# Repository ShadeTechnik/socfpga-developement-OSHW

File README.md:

# socfpga-developement-OSHW
hardware and software development for socfpga, open source

Copyright 2019 Shade Technik

<br />This work is licensed under a <a rel="license" href="http://creativecommons.org/licenses/by-sa/4.0/">Creative Commons Attribution-ShareAlike 4.0 International License</a>.

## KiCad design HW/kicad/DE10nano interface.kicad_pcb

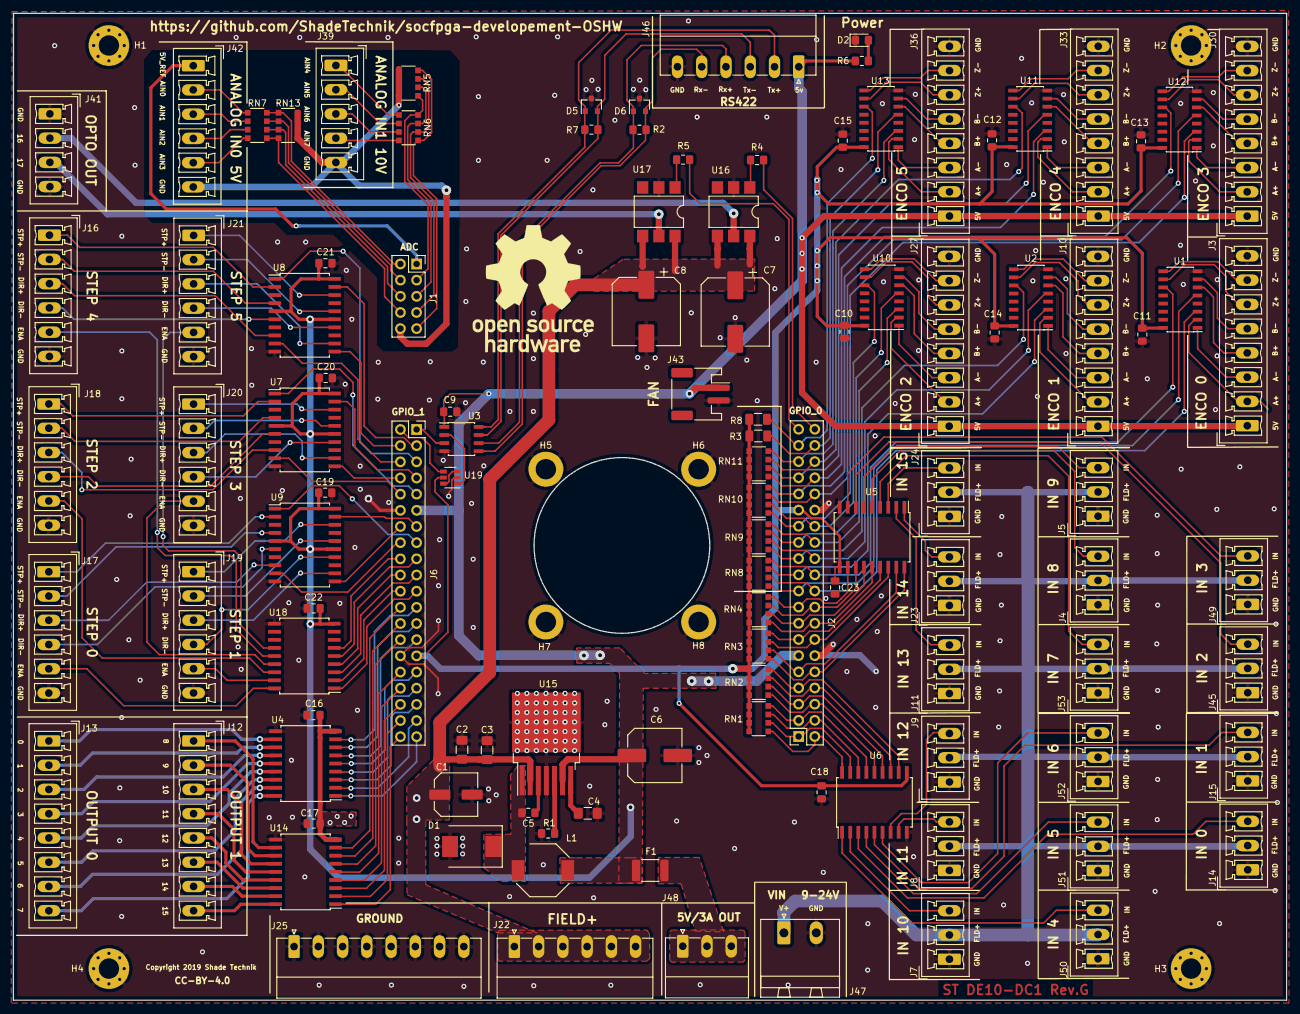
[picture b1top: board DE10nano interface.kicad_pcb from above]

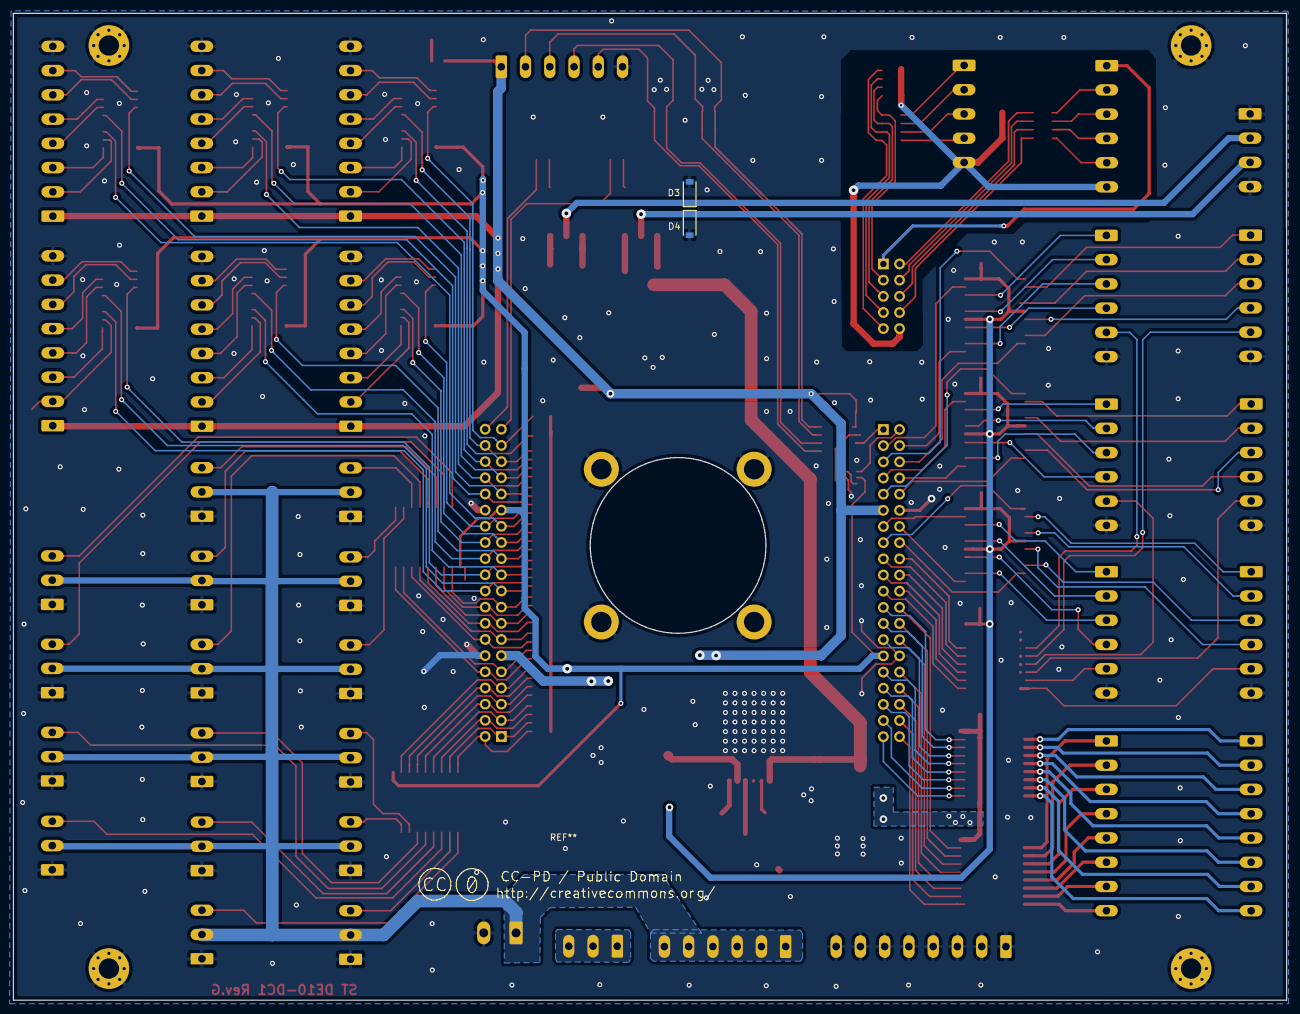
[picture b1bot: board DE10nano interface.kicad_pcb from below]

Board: 2 copper layers, 200.0 x 155.0 mm, 120 parts (2 on the bottom side), 208 nets.

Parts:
C1: 22uf; C_Elec_6.3x7.7
C2, C3: 6.8uf; C_1206_3216Metric_Pad1.42x1.75mm_HandSolder
C4: 1uf; C_1206_3216Metric_Pad1.42x1.75mm_HandSolder
C5: 10nF; C_0805_2012Metric_Pad1.15x1.40mm_HandSolder
C6: 180uF; C_Elec_8x10.2
C7, C8: 100uF; CP_Elec_10x10.5
C9: 0.1uF; C_0805_2012Metric_Pad1.15x1.40mm_HandSolder
C10, C11, C12, C13, C14, C15, C16, C17, C18, C19, C20, C21, C22, C23: .1uf; C_0805_2012Metric_Pad1.15x1.40mm_HandSolder
D1: 60v 5a; D_SMC
D2: LED_PWR; LED_0805_2012Metric_Pad1.15x1.40mm_HandSolder
D3, D4: D_Schottky; D_SOD-123
D5, D6: SM712; SOT-23
F1: 1.5Ahold/3Atrip; Fuse_1812_4532Metric_Pad1.30x3.40mm_HandSolder
H1, H2, H3, H4: MountingHole_Pad; MountingHole_3.2mm_M3_Pad_Via
H5, H6, H7, H8: MountingHole_Pad; MountingHole_3.2mm_M3_ISO14580_Pad
J1: DE0_ADC; PinSocket_2x05_P2.54mm_Vertical
J2: DE0_GPIO_0; PinSocket_2x20_P2.54mm_Vertical
J3: ENC0_IN; PhoenixContact_MCV_1,5_8-G-3.81_1x08_P3.81mm_Vertical
J4: Conn_In_8; PhoenixContact_MCV_1,5_3-G-3.81_1x03_P3.81mm_Vertical
J5: Conn_In_9; PhoenixContact_MCV_1,5_3-G-3.81_1x03_P3.81mm_Vertical
J6: DE0_GPIO_1; PinSocket_2x20_P2.54mm_Vertical
J7: Conn_In_10; PhoenixContact_MCV_1,5_3-G-3.81_1x03_P3.81mm_Vertical
J8: Conn_In_11; PhoenixContact_MCV_1,5_3-G-3.81_1x03_P3.81mm_Vertical
J9: Conn_In_12; PhoenixContact_MCV_1,5_3-G-3.81_1x03_P3.81mm_Vertical
J10: ENC1_IN; PhoenixContact_MCV_1,5_8-G-3.81_1x08_P3.81mm_Vertical
J11: Conn_In_13; PhoenixContact_MCV_1,5_3-G-3.81_1x03_P3.81mm_Vertical
J12: Conn_Out_1; PhoenixContact_MCV_1,5_8-G-3.81_1x08_P3.81mm_Vertical
J13: Conn_Out_0; PhoenixContact_MCV_1,5_8-G-3.81_1x08_P3.81mm_Vertical
J14: Conn_In_0; PhoenixContact_MCV_1,5_3-G-3.81_1x03_P3.81mm_Vertical
J15: Conn_In_1; PhoenixContact_MCV_1,5_3-G-3.81_1x03_P3.81mm_Vertical
J16: StepGen4; PhoenixContact_MCV_1,5_6-G-3.81_1x06_P3.81mm_Vertical
J17: StepGen0; PhoenixContact_MCV_1,5_6-G-3.81_1x06_P3.81mm_Vertical
J18: StepGen2; PhoenixContact_MCV_1,5_6-G-3.81_1x06_P3.81mm_Vertical
J19: StepGen1; PhoenixContact_MCV_1,5_6-G-3.81_1x06_P3.81mm_Vertical
J20: StepGen3; PhoenixContact_MCV_1,5_6-G-3.81_1x06_P3.81mm_Vertical
J21: StepGen5; PhoenixContact_MCV_1,5_6-G-3.81_1x06_P3.81mm_Vertical
J22: Conn_Field+; PhoenixContact_MC_1,5_6-G-3.81_1x06_P3.81mm_Horizontal
J23: Conn_In_14; PhoenixContact_MCV_1,5_3-G-3.81_1x03_P3.81mm_Vertical
J24: Conn_In_15; PhoenixContact_MCV_1,5_3-G-3.81_1x03_P3.81mm_Vertical
J25: Conn_01x08-Connector_Generic; PhoenixContact_MC_1,5_8-G-3.81_1x08_P3.81mm_Horizontal
J27: ENC2_IN; PhoenixContact_MCV_1,5_8-G-3.81_1x08_P3.81mm_Vertical
J30: ENC3_IN; PhoenixContact_MCV_1,5_8-G-3.81_1x08_P3.81mm_Vertical
J33: ENC4_IN; PhoenixContact_MCV_1,5_8-G-3.81_1x08_P3.81mm_Vertical
J36: ENC5_IN; PhoenixContact_MCV_1,5_8-G-3.81_1x08_P3.81mm_Vertical
J39: Conn_ADC_1_10V; PhoenixContact_MCV_1,5_5-G-3.81_1x05_P3.81mm_Vertical
J41: Conn_Opto_out; PhoenixContact_MCV_1,5_4-G-3.81_1x04_P3.81mm_Vertical
J42: Conn_ADC_0_5V; PhoenixContact_MCV_1,5_6-G-3.81_1x06_P3.81mm_Vertical
J43: Conn_Fan; JST_PH_S2B-PH-SM4-TB_1x02-1MP_P2.00mm_Horizontal
J45: Conn_In_2; PhoenixContact_MCV_1,5_3-G-3.81_1x03_P3.81mm_Vertical
J46: Conn_RS422; PhoenixContact_MC_1,5_6-G-3.81_1x06_P3.81mm_Horizontal
J47: Conn_VIN; PhoenixContact_MSTBA_2,5_2-G-5,08_1x02_P5.08mm_Horizontal
J48: Conn_5v; PhoenixContact_MC_1,5_3-G-3.81_1x03_P3.81mm_Horizontal
J49: Conn_In_3; PhoenixContact_MCV_1,5_3-G-3.81_1x03_P3.81mm_Vertical
J50: Conn_In_4; PhoenixContact_MCV_1,5_3-G-3.81_1x03_P3.81mm_Vertical
J51: Conn_In_5; PhoenixContact_MCV_1,5_3-G-3.81_1x03_P3.81mm_Vertical
J52: Conn_In_6; PhoenixContact_MCV_1,5_3-G-3.81_1x03_P3.81mm_Vertical
J53: Conn_In_7; PhoenixContact_MCV_1,5_3-G-3.81_1x03_P3.81mm_Vertical
L1: 4.7uH; L_Bourns-SRU8043
R1: 8k2; R_0805_2012Metric_Pad1.15x1.40mm_HandSolder
R2, R7: 120R; R_0805_2012Metric_Pad1.15x1.40mm_HandSolder
R3, R8: 4.7k; R_1206_3216Metric
R4, R5: 680R; R_0805_2012Metric_Pad1.15x1.40mm_HandSolder
R6: 180R; R_0805_2012Metric_Pad1.15x1.40mm_HandSolder
RN1, RN2, RN3, RN4, RN8, RN9, RN10, RN11: 4.7k; R_Array_Convex_4x1206
RN5, RN13: 10k; R_Array_Convex_4x1206
RN6: 15k; R_Array_Convex_4x1206
RN7: 2.2k; R_Array_Convex_4x1206
U1, U2, U10, U11, U12, U13: AM26LS32; SOIC-16_3.9x9.9mm_P1.27mm
U3: DS89C21; SOIC-8_3.9x4.9mm_P1.27mm
U4, U14, U18: MIC2981; SOIC-18W_7.5x11.6mm_P1.27mm
U5, U6: ULN2803A; SOIC-18W_7.5x11.6mm_P1.27mm
U7, U8, U9: SN75174DWR; SOIC-20W_7.5x12.8mm_P1.27mm
U15: LM22679; TO-263-7_TabPin4
U16, U17: SMP-1A36-6S; SMDIP-6_W7.62mm
U19: 74LVC2G04; SOT-23-6

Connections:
3.3v: C10.2, C11.2, C12.2, C13.2, C14.2, C15.2, C18.2, C23.2, J2.29, J6.29, R3.2, R8.2, RN1.1, RN1.2, RN1.3, RN1.4, RN2.1, RN2.2, RN2.3, RN2.4, RN3.1, RN3.2, RN3.3, RN3.4, RN4.1, RN4.2, RN4.3, RN4.4, RN8.1, RN8.2, RN8.3, RN8.4, RN9.1, RN9.2, RN9.3, RN9.4, RN10.1, RN10.2, RN10.3, RN10.4, RN11.1, RN11.2, RN11.3, RN11.4, U1.16, U2.16, U5.10, U6.10, U10.16, U11.16, U12.16, U13.16, U19.5
5v: C6.1, C9.2, C19.2, C20.2, C21.2, C22.2, F1.2, J2.11, J3.1, J6.11, J10.1, J27.1, J30.1, J33.1, J36.1, J43.1, J46.1, L1.2, R6.1, U3.1, U7.5, U7.15, U7.20, U8.5, U8.15, U8.20, U9.5, U9.15, U9.20, U15.6, U18.9
5v_ADC_REF: J1.1, J42.1
/Output Interface/0: J13.1, U4.11
/Output Interface/1: J13.2, U4.12
/Output Interface/2: J13.3, U4.13
/Output Interface/3: J13.4, U4.14
/Output Interface/4: J13.5, U4.15
/Output Interface/5: J13.6, U4.16
/Output Interface/6: J13.7, U4.17
/Output Interface/7: J13.8, U4.18
/Output Interface/8: J12.1, U14.11
/Output Interface/9: J12.2, U14.12
/Output Interface/10: J12.3, U14.13
/Output Interface/11: J12.4, U14.14
/Output Interface/12: J12.5, U14.15
/Output Interface/13: J12.6, U14.16
/Output Interface/14: J12.7, U14.17
/Output Interface/15: J12.8, U14.18
/Output Interface/16: D3.1, J41.2, U16.5
/Output Interface/17: D4.1, J41.3, U17.5
/RS422 Interface/Rx+: D5.2, J46.3, R7.2, U3.7
/RS422 Interface/Rx-: D5.1, J46.2, R7.1, U3.8
/RS422 Interface/Tx+: D6.2, J46.5, R2.1, U3.5
/RS422 Interface/Tx-: D6.1, J46.4, R2.2, U3.6
AGND: J1.10, J39.5, J42.6, RN5.5, RN5.6, RN5.7, RN5.8, RN13.5, RN13.6, RN13.7, RN13.8
AIN0: J1.2, RN7.8, RN13.1
AIN1: J1.3, RN5.1, RN6.8
AIN2: J1.4, RN7.7, RN13.2
AIN3: J1.5, RN5.2, RN6.7
AIN4: J1.6, RN7.6, RN13.3
AIN5: J1.7, RN5.3, RN6.6
AIN6: J1.8, RN7.5, RN13.4
AIN7: J1.9, RN5.4, RN6.5
DGND: C1.2, C2.2, C3.2, C4.2, C6.2, C7.2, C8.2, C9.1, C10.1, C11.1, C12.1, C13.1, C14.1, C15.1, C16.2, C17.2, C18.1, C19.1, C20.1, C21.1, C22.1, C23.1, D1.2, D2.1, D3.2, D4.2, D5.3, D6.3, H1.1, H2.1, H3.1, H4.1, H5.1, H6.1, H7.1, H8.1, J2.12, J2.30, J3.8, J4.1, J5.1, J6.12, J6.30, J7.1, J8.1, J9.1, J10.8, J11.1, J14.1, J15.1, J16.6, J17.6, J18.6, J19.6, J20.6, J21.6, J23.1, J24.1, J25.1, J25.2, J25.3, J25.4, J25.5, J25.6, J25.7, J25.8, J27.8, J30.8, J33.8, J36.8, J41.1, J41.4, J43.2, J45.1, J46.6, J47.2, J49.1, J50.1, J51.1, J52.1, J53.1, R1.2, U1.8, U2.8, U3.4, U4.10, U5.9, U6.9, U7.10, U8.10, U9.10, U10.8, U11.8, U12.8, U13.8, U14.10, U15.4, U16.2, U17.2, U18.10, U19.2
DIR0: J6.16, U9.9
DIR1: J6.14, U9.11
DIR2: J6.10, U7.9
DIR3: J6.8, U7.11
DIR4: J6.6, U8.9
DIR5: J6.4, U8.11
DIR_CHAN0+: J17.3, U9.8
DIR_CHAN0-: J17.4, U9.6
DIR_CHAN1+: J19.3, U9.12
DIR_CHAN1-: J19.4, U9.14
DIR_CHAN2+: J18.3, U7.8
DIR_CHAN2-: J18.4, U7.6
DIR_CHAN3+: J20.3, U7.12
DIR_CHAN3-: J20.4, U7.14
DIR_CHAN4+: J16.3, U8.8
DIR_CHAN4-: J16.4, U8.6
DIR_CHAN5+: J21.3, U8.12
DIR_CHAN5-: J21.4, U8.14
ENC0_A: J2.20, RN8.6, U1.3
ENC0_B: J2.19, RN8.5, U1.5
ENC0_CHAN_A+: J3.2, U1.2
ENC0_CHAN_A-: J3.3, U1.1
ENC0_CHAN_B+: J3.4, U1.6
ENC0_CHAN_B-: J3.5, U1.7
ENC0_CHAN_Z+: J3.6, U1.10
ENC0_CHAN_Z-: J3.7, U1.9
ENC0_Z: J2.22, RN8.8, U1.11
ENC1_A: J2.21, RN8.7, U2.3
ENC1_B: J2.24, RN9.6, U2.5
ENC1_CHAN_A+: J10.2, U2.2
ENC1_CHAN_A-: J10.3, U2.1
ENC1_CHAN_B+: J10.4, U2.6
ENC1_CHAN_B-: J10.5, U2.7
ENC1_CHAN_Z+: J10.6, U2.10
ENC1_CHAN_Z-: J10.7, U2.9
ENC1_Z: J2.23, RN9.5, U2.11
ENC2_A: J2.26, RN9.8, U10.3
ENC2_B: J2.25, RN9.7, U10.5
ENC2_CHAN_A+: J27.2, U10.2
ENC2_CHAN_A-: J27.3, U10.1
ENC2_CHAN_B+: J27.4, U10.6
ENC2_CHAN_B-: J27.5, U10.7
ENC2_CHAN_Z+: J27.6, U10.10
ENC2_CHAN_Z-: J27.7, U10.9
ENC2_Z: J2.28, RN10.6, U10.11
ENC3_A: J2.27, RN10.5, U12.3
ENC3_B: J2.32, RN10.7, U12.5
ENC3_CHAN_A+: J30.2, U12.2
ENC3_CHAN_A-: J30.3, U12.1
ENC3_CHAN_B+: J30.4, U12.6
ENC3_CHAN_B-: J30.5, U12.7
ENC3_CHAN_Z+: J30.6, U12.10
ENC3_CHAN_Z-: J30.7, U12.9
ENC3_Z: J2.31, RN10.8, U12.11
ENC4_A: J2.34, RN11.5, U11.3
ENC4_B: J2.33, RN11.6, U11.5
ENC4_CHAN_A+: J33.2, U11.2
ENC4_CHAN_A-: J33.3, U11.1
ENC4_CHAN_B+: J33.4, U11.6
ENC4_CHAN_B-: J33.5, U11.7
ENC4_CHAN_Z+: J33.6, U11.10
ENC4_CHAN_Z-: J33.7, U11.9
ENC4_Z: J2.36, RN11.7, U11.11
ENC5_A: J2.35, RN11.8, U13.3
ENC5_B: J2.38, R3.1, U13.5
ENC5_CHAN_A+: J36.2, U13.2
ENC5_CHAN_A-: J36.3, U13.1
ENC5_CHAN_B+: J36.4, U13.6
ENC5_CHAN_B-: J36.5, U13.7
ENC5_CHAN_Z+: J36.6, U13.10
ENC5_CHAN_Z-: J36.7, U13.9
ENC5_Z: J2.37, R8.1, U13.11
FieldV+: C1.1, C2.1, C3.1, C7.1, C8.1, C16.1, C17.1, J4.2, J5.2, J7.2, J8.2, J9.2, J11.2, J14.2, J15.2, J22.1, J22.2, J22.3, J22.4, J22.5, J22.6, J23.2, J24.2, J45.2, J47.1, J49.2, J50.2, J51.2, J52.2, J53.2, U4.9, U14.9, U15.2, U16.4, U16.6, U17.4, U17.6
GPIO_IN_0: J2.10, RN3.5, U5.18
GPIO_IN_1: J2.9, RN3.6, U5.17
GPIO_IN_2: J2.14, RN3.7, U5.16
GPIO_IN_3: J2.13, RN3.8, U5.15
GPIO_IN_4: J2.16, RN4.5, U5.14
GPIO_IN_5: J2.15, RN4.6, U5.13
GPIO_IN_6: J2.18, RN4.7, U5.12
GPIO_IN_7: J2.17, RN4.8, U5.11
GPIO_IN_8: J2.2, RN1.5, U6.18
GPIO_IN_9: J2.1, RN1.6, U6.17
GPIO_IN_10: J2.4, RN1.7, U6.16
GPIO_IN_11: J2.3, RN1.8, U6.15
GPIO_IN_12: J2.6, RN2.5, U6.14
GPIO_IN_13: J2.5, RN2.6, U6.13
GPIO_IN_14: J2.8, RN2.7, U6.12
GPIO_IN_15: J2.7, RN2.8, U6.11
GPIO_OUT_0: J6.23, U4.8
GPIO_OUT_1: J6.25, U4.7
GPIO_OUT_2: J6.27, U4.6
GPIO_OUT_3: J6.31, U4.5
GPIO_OUT_4: J6.33, U4.4
GPIO_OUT_5: J6.35, U4.3
GPIO_OUT_6: J6.37, U4.2
GPIO_OUT_7: J6.39, U4.1
GPIO_OUT_8: J6.24, U14.8
GPIO_OUT_9: J6.26, U14.7
GPIO_OUT_10: J6.28, U14.6
GPIO_OUT_11: J6.32, U14.5
GPIO_OUT_12: J6.34, U14.4
GPIO_OUT_13: J6.36, U14.3
GPIO_OUT_14: J6.38, U14.2
GPIO_OUT_15: J6.40, U14.1
GPIO_OUT_16: J2.40, R4.2
GPIO_OUT_17: J2.39, R5.2
unnamed: C4.1, U15.7
unnamed: C5.1, U15.3
unnamed: C5.2, D1.1, L1.1, U15.1
unnamed: D2.2, R6.2
unnamed: F1.1, J48.1, J48.2, J48.3
unnamed: J4.3, U5.5
unnamed: J5.3, U5.6
unnamed: J7.3, U6.2
unnamed: J8.3, U6.8
unnamed: J9.3, U6.7
unnamed: J11.3, U5.2
unnamed: J14.3, U6.3
unnamed: J15.3, U6.5
unnamed: J23.3, U5.1
unnamed: J24.3, U5.3
unnamed: J39.1, RN6.1
unnamed: J39.2, RN6.2
unnamed: J39.3, RN6.3
unnamed: J39.4, RN6.4
unnamed: J42.2, RN7.1
unnamed: J42.3, RN7.2
unnamed: J42.4, RN7.3
unnamed: J42.5, RN7.4
unnamed: J45.3, U5.7
unnamed: J49.3, U5.8
unnamed: J50.3, U6.1
unnamed: J51.3, U6.4
unnamed: J52.3, U6.6
unnamed: J53.3, U5.4
unnamed: R1.1, U15.5
unnamed: R4.1, U16.1
unnamed: R5.1, U17.1
unnamed: U3.2, U19.1
unnamed: U19.3, U19.6
Rx: J6.2, U19.4
S-D_ENA_0: J6.21, U18.1
S-D_ENA_1: J6.22, U18.2
S-D_ENA_2: J6.19, U18.3
S-D_ENA_3: J6.20, U18.4
S-D_ENA_4: J6.17, U18.5
S-D_ENA_5: J6.18, U18.6
STEP0: J6.15, U9.1
STEP1: J6.13, U9.19
STEP2: J6.9, U7.1
STEP3: J6.7, U7.19
STEP4: J6.5, U8.1
STEP5: J6.3, U8.19
STEP_CHAN0+: J17.1, U9.2
STEP_CHAN0-: J17.2, U9.4
STEP_CHAN1+: J19.1, U9.18
STEP_CHAN1-: J19.2, U9.16
STEP_CHAN2+: J18.1, U7.2
STEP_CHAN2-: J18.2, U7.4
STEP_CHAN3+: J20.1, U7.18
STEP_CHAN3-: J20.2, U7.16
STEP_CHAN4+: J16.1, U8.2
STEP_CHAN4-: J16.2, U8.4
STEP_CHAN5+: J21.1, U8.18
STEP_CHAN5-: J21.2, U8.16
STEP_ENA_0: J17.5, U18.18
STEP_ENA_1: J19.5, U18.17
STEP_ENA_2: J18.5, U18.16
STEP_ENA_3: J20.5, U18.15
STEP_ENA_4: J16.5, U18.14
STEP_ENA_5: J21.5, U18.13
Tx: J6.1, U3.3

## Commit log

2019-09-23 Create DE10-Nano
2019-09-23 sorting
2019-09-23 deleted: HW/kicad/DE10nano interface-cache.lib deleted: HW/kicad/DE10nano interface-rescue.dcm deleted: HW/kicad/DE10nano interface-rescue.lib deleted: HW/kicad/DE10nano interface.bak deleted: HW/kic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
2019-09-23 new file: DE10-Nano/mksocfpga Config files/ADC_component/adc.comp new file: DE10-Nano/mksocfpga Config files/ADC_component/adc8.comp
2019-09-23 renamed: DE10-Nano/HW/kicad/DE10nano interface-cache.lib -> DE10-Nano/ST-DC1 daughtercard/HW/kicad/DE10nano interface-cache.lib renamed: DE10-Nano/HW/kicad/DE10nano interface-rescue.dcm -> DE10-Nano/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
2019-09-23 new file: DE10-Nano/ST-DC1 daughtercard/HW/kicad/DE10nano interface.jpg modified: README.md
2019-09-23 modified: README.md
2019-09-25 Add Artwork to PCB: DE10-Nano/ST-DC1 daughtercard/HW/kicad/DE10nano interface-cache.lib Add Artwork to PCB: DE10-Nano/ST-DC1 daughtercard/HW/kicad/DE10nano interface.jpg Add termination Resistors to 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
2019-09-27 new file: DE10-Nano/ST-DC1 daughtercard/HW/kicad/_autosave-DE10nano interface.kicad_pcb version lacks usefullness: DE10-Nano/ST-DC1 daughtercard/mksocfpga Config files/ADC_component/adc8.comp modifie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
2019-09-29 Add component doc: DE10-Nano/ST-DC1 daughtercard/mksocfpga Config files/ADC_component/vari-bit-depth.txt replace old component with more functional component: DE10-Nano/ST-DC1 daughtercard/mksocfpga 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
2019-10-02 remove commentary

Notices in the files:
HW/kicad/DE10nano interface.kicad_pcb:
CC-BY-4.0
